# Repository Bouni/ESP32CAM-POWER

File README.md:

# ESP32-CAM POWER BOARD

This board is meant to act as a carrier board for an ESP32-CAM Module taht supplies it with power and allows for up to 24VDC supply voltage.

The DC-DC converter board used is of [AliExpress](https://de.aliexpress.com/item/4000186205198.html).

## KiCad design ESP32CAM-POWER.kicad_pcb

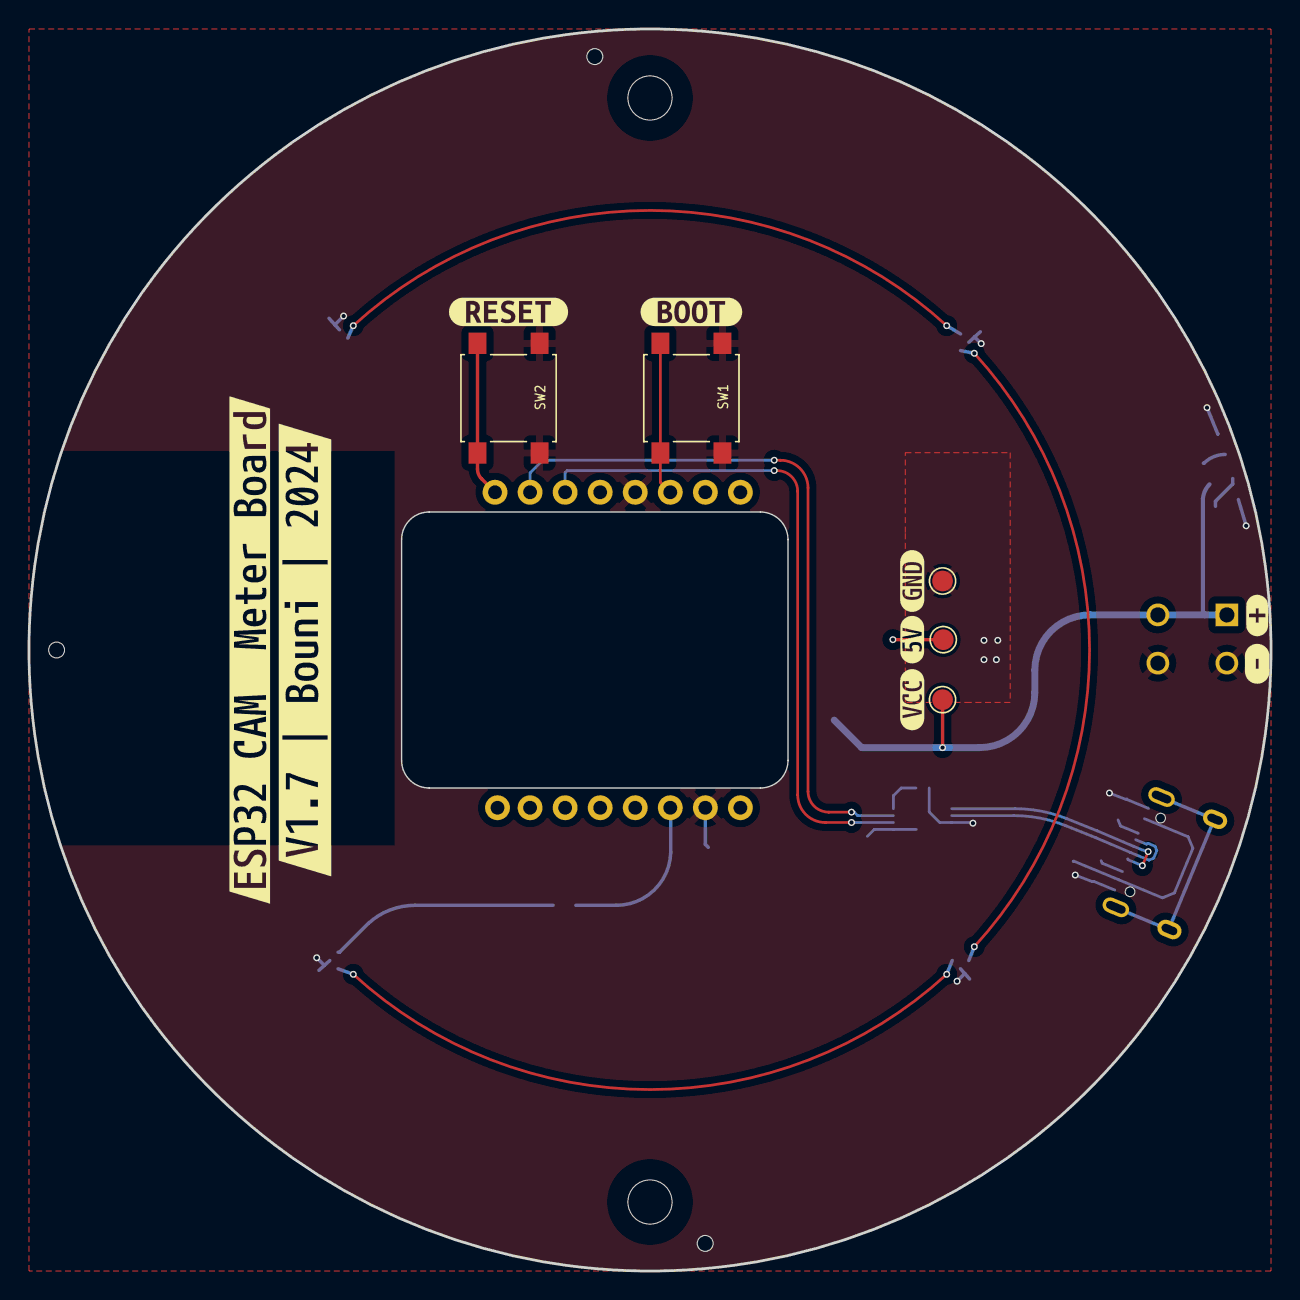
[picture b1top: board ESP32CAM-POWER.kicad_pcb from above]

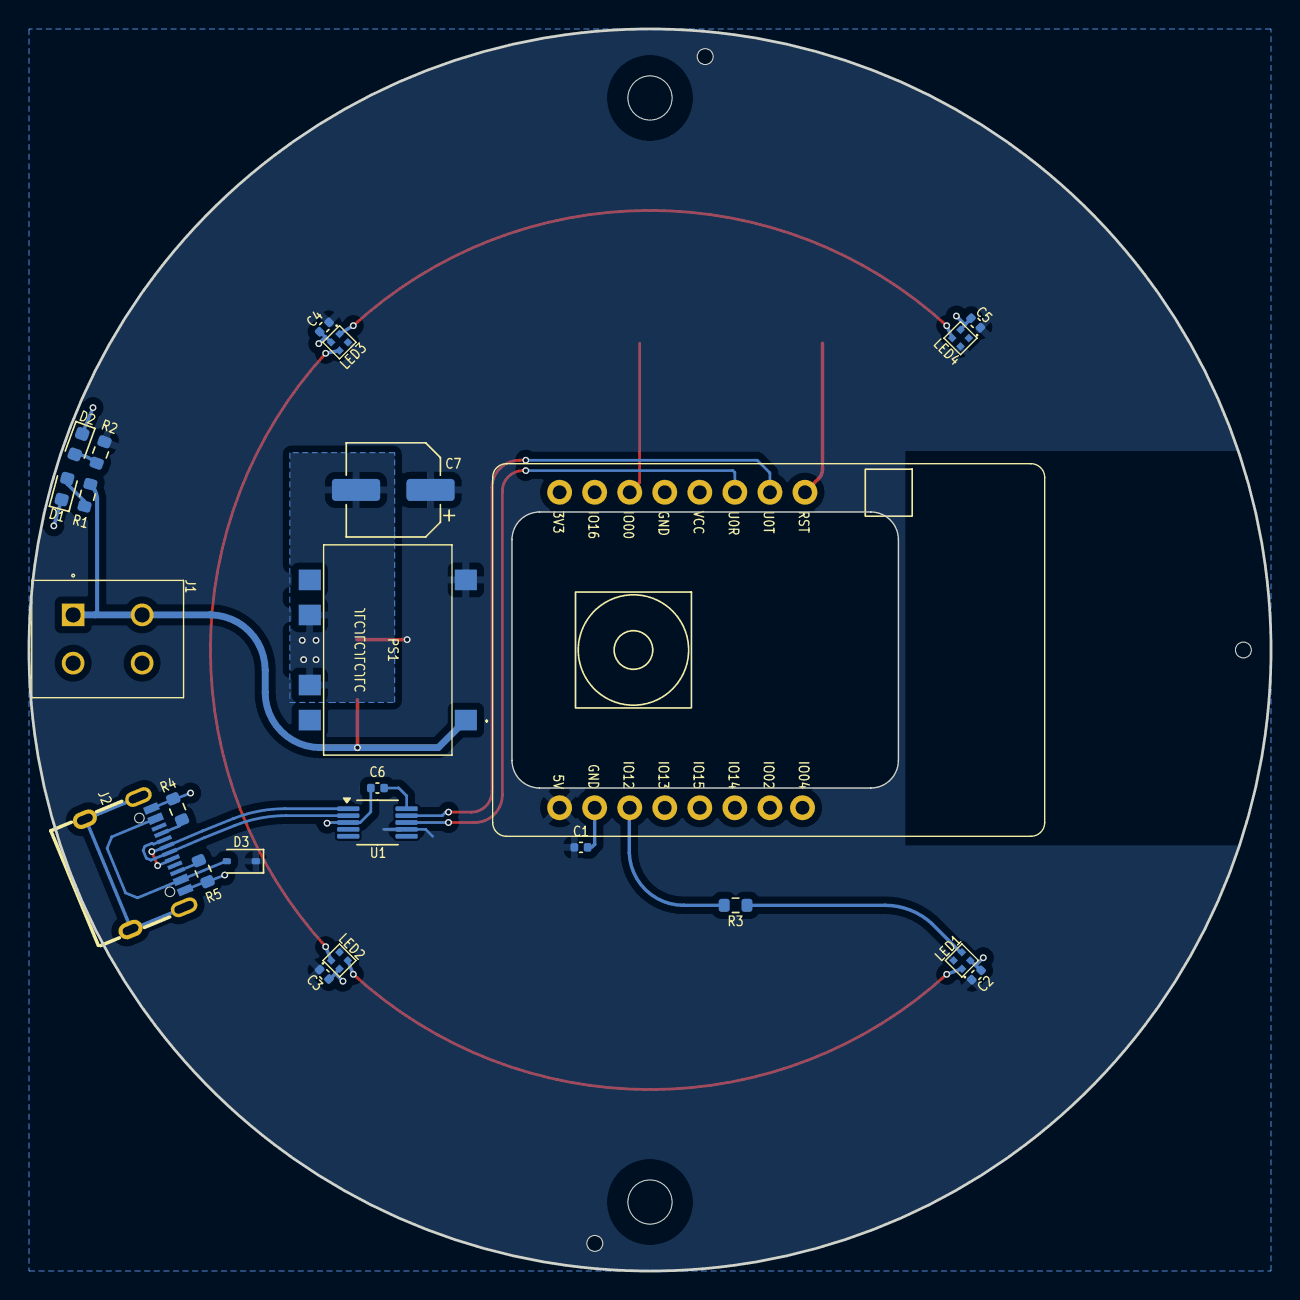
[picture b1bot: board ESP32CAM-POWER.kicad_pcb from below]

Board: 2 copper layers, 90.0 x 90.0 mm, 43 parts (24 on the bottom side), 20 nets.

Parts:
C1, C2, C3, C4, C5, C6: 0.1uF; C_0402_1005Metric
C7: 100uF; CP_Elec_6.3x5.8
D1: LED_B; LED_0603_1608Metric
D2: LED_G; LED_0603_1608Metric
D3: 1N5819WS; D_SOD-323
H1, H2: MountingHole; MountingHole_3.2mm_M3_ISO14580
J1: Screw_Terminal_01x02; 1861933
J2: USB_C_Receptacle_USB2.0_16P; USB-C-SMD_TYPE-C-6PIN-2MD-073
LED1, LED2, LED3, LED4: XL-1010RGBC-WS2812B; LED-SMD_4P-L1.0-W1.0-TL_XL-1010RGBC-WS2812B
PS1: TSR_1-2450SM; TSR124120SM
R1: 10k; R_0603_1608Metric
R2: 680; R_0603_1608Metric
R3: 470; R_0603_1608Metric
R4, R5: 5K1; R_0603_1608Metric
SW1, SW2: SW_Omron_B3S; SW_SPST_B3S-1000
TH: ToolingHole
TH#2, TH#3: ToolingHole
TP1, TP2, TP3: TestPoint; TestPoint_Pad_D1.5mm
U1: CH340X; MSOP-10_3x3mm_P0.5mm
U2: ESP32-CAM
kibuzzard-66C81FD1: G***; kibuzzard-66C81FD1
kibuzzard-66C81FE3: G***; kibuzzard-66C81FE3
kibuzzard-66C7590B: G***; kibuzzard-66C7590B
kibuzzard-66C8202D: G***; kibuzzard-66C8202D
kibuzzard-66C75903: G***; kibuzzard-66C75903
kibuzzard-66C82011: G***; kibuzzard-66C82011
kibuzzard-66CDCC8A: G***; kibuzzard-66CDCC8A
kibuzzard-66CDCC90: G***; kibuzzard-66CDCC90
kibuzzard-66CDCC95: G***; kibuzzard-66CDCC95

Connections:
+5V: C1.1, C2.1, C3.1, C4.1, C5.1, C7.1, D3.1 (K), LED1.2 (VDD), LED2.2 (VDD), LED3.2 (VDD), LED4.2 (VDD), PS1.5 (+VOUT), R2.1, TP2.1, U1.7 (VCC), U2.1 (5V)
/D+: J2.A6 (D+), J2.B6 (D+), U1.1 (UD+)
/D-: J2.A7 (D-), J2.B7 (D-), U1.2 (UD-)
BOOT: SW1.2, U2.11 (IO00)
D1: LED1.1 (DOUT), LED2.4 (DIN)
D2: LED2.1 (DOUT), LED3.4 (DIN)
D3: LED3.1 (DOUT), LED4.4 (DIN)
GND: C1.2, C2.2, C3.2, C4.2, C5.2, C6.1, C7.2, D1.1 (K), D2.1 (K), J1.2, J2.A1 (GND), J2.B1 (GND), LED1.3 (GND), LED2.3 (GND), LED3.3 (GND), LED4.3 (GND), PS1.7 (GND_1), PS1.9 (GND_2), R4.2, R5.2, SW1.1, SW2.1, TP1.1, U1.3 (GND), U2.2 (GND), U2.12 (GND)
LED: R3.1, U2.3 (IO12)
unnamed: D1.2 (A), R1.2
unnamed: D2.2 (A), R2.2
unnamed: D3.2 (A), J2.A4 (VBUS), J2.B4 (VBUS)
unnamed: J2.A5 (CC1), R4.1
unnamed: J2.B5 (CC2), R5.1
unnamed: LED1.4 (DIN), R3.2
unnamed: C6.2, U1.10 (V3)
RESET: SW2.2, U2.16 (RST)
RXD: U1.9 (RXD), U2.15 (U0T)
TXD: U1.8 (TXD), U2.14 (U0R)
VCC: J1.1, PS1.1 (+VIN), R1.1, TP3.1

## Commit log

2021-11-24 some chages for V1.3
2021-12-30 serveral changes, add USB, still a bit messy
2021-12-30 minor cleanups
2022-06-02 massiv rework, mostly simplified the project
2022-06-02 Add notes to schematic
2022-06-02 add Schmatic as PDF, add top and bottom images
2022-06-02 add README
2022-06-02 fixed wrong link to picture in README
2022-06-23 fixed short circuit caused by mounting holes
2022-06-24 fixed several bugs, replaced DCDC Module with onboard step down
2022-06-24 last cleanups
2024-10-21 Ooctober 2024 Update
